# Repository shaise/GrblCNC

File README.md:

# GrblCNC
A C# Clone to LinuxCNC that works with GRBL CNC driver  
#### This project is done in parallel with a compatible Grbl driver firmware
* [Click here for project page](https://github.com/shaise/grblHAL_CNC3040)
```diff
- This is a work in progress, only basic stuff are operational  
```
## Software
### Screen preview 

## Hardware
* [Click here for firmware project page](https://github.com/shaise/grblHAL_CNC3040)
* [Click here for project progress](PROGRESS.md)
* [Click here for list of added capabilities](EXTENTIONS.md)
### GRBL for Chinese CNC3040-like machines. WIP. 
### Based on STM32F103C8T6 "Bluepill" boards with customized grblHAL firmware 
#### Project goals: 
* Develop simple open hardware plug to replace the vanishing parallel port
    - Support configurable pin assignments
    - Support extra controls not available on CNC3040 such as mist, flood, spindle RPM reader
* Add support for more axis. (at least add A axis)
* Support other features that LinuxCNC have

## Development Environment
|                      |                          |
|----------------------|--------------------------|
| **IDE**              | STM32CubeIDE v1.2.0      |
| **Controller board** | STM32F103C8T6 (Bluepill) |

## Reference
- GRBL CNC controller ported to STM32 controller (and others)
```https://github.com/terjeio/grblHAL```
- GRBL CNC controller
```https://github.com/gnea/grbl```

## Pin Diagram

## GRBL dongle for CNC3040 concept art:

### Back side

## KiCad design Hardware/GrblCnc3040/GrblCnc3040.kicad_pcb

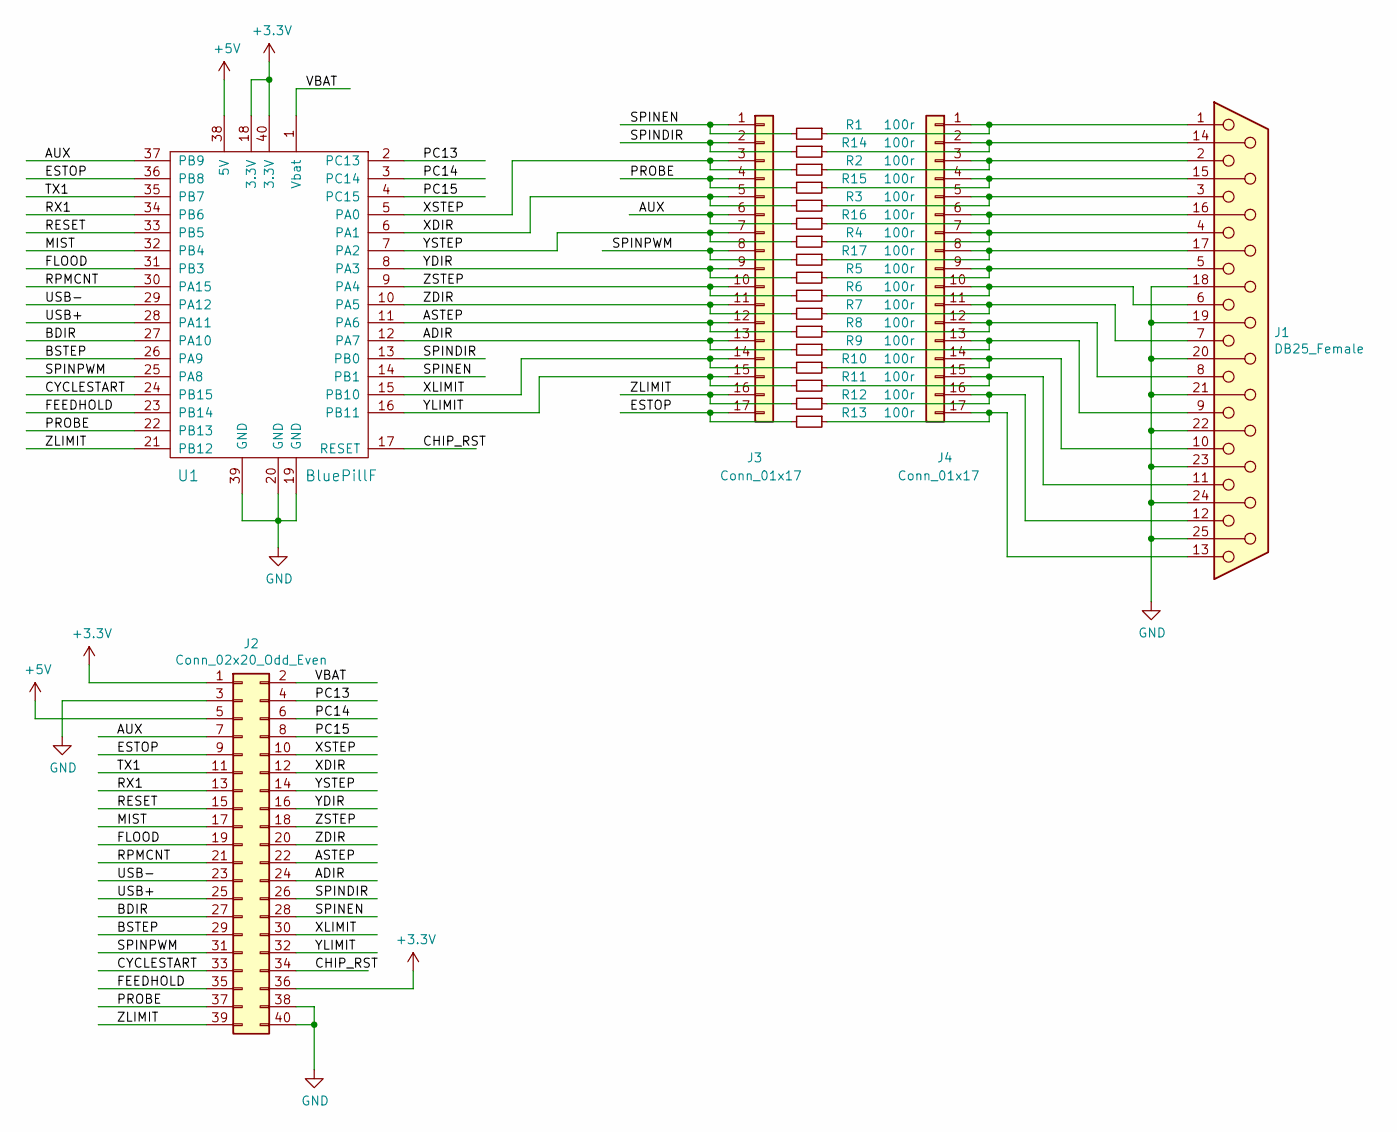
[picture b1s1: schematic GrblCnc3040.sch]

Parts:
J1: DB25_Female; DSUB-25_Female_Horizontal_P2.77x2.84mm_EdgePinOffset4.94mm_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
J2: Conn_02x20_Odd_Even; PinSocket_2x20_P2.54mm_Vertical
J3, J4: Conn_01x17; PinHeader_1x17_P2.54mm_Vertical
R1, R2, R3, R4, R5, R6, R7, R8, R9, R10, R11, R12, R13, R14, R15, R16, R17: 100r; R_0603_1608Metric
U1: BluePillF; BluePill_STM32F103C

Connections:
+3V3: J2.1, J2.36, U1.18 (3.3V), U1.40 (3.3V)
+5V: J2.5, U1.38 (5V)
/ADIR: J2.24, J3.13, R9.2, U1.12 (PA7)
/ASTEP: J2.22, J3.12, R8.2, U1.11 (PA6)
/AUX: J2.7, J3.6, R16.2, U1.37 (PB9)
/BDIR: J2.27, U1.27 (PA10)
/BSTEP: J2.29, U1.26 (PA9)
/CHIP_RST: J2.34, U1.17 (RESET)
/CYCLESTART: J2.33, U1.24 (PB15)
/ESTOP: J2.9, J3.17, R13.2, U1.36 (PB8)
/FEEDHOLD: J2.35, U1.23 (PB14)
/FLOOD: J2.19, U1.31 (PB3)
/MIST: J2.17, U1.32 (PB4)
/PC13: J2.4, U1.2 (PC13)
/PC14: J2.6, U1.3 (PC14)
/PC15: J2.8, U1.4 (PC15)
/PROBE: J2.37, J3.4, R15.2, U1.22 (PB13)
/RESET: J2.15, U1.33 (PB5)
/RPMCNT: J2.21, U1.30 (PA15)
/RX1: J2.13, U1.34 (PB6)
/SPINDIR: J2.26, J3.2, R14.2, U1.13 (PB0)
/SPINEN: J2.28, J3.1, R1.2, U1.14 (PB1)
/SPINPWM: J2.31, J3.8, R17.2, U1.25 (PA8)
/TX1: J2.11, U1.35 (PB7)
/USB+: J2.25, U1.28 (PA11)
/USB-: J2.23, U1.29 (PA12)
/VBAT: J2.2, U1.1 (Vbat)
/XDIR: J2.12, J3.5, R3.2, U1.6 (PA1)
/XLIMIT: J2.30, J3.14, R10.2, U1.15 (PB10)
/XSTEP: J2.10, J3.3, R2.2, U1.5 (PA0)
/YDIR: J2.16, J3.9, R5.2, U1.8 (PA3)
/YLIMIT: J2.32, J3.15, R11.2, U1.16 (PB11)
/YSTEP: J2.14, J3.7, R4.2, U1.7 (PA2)
/ZDIR: J2.20, J3.11, R7.2, U1.10 (PA5)
/ZLIMIT: J2.39, J3.16, R12.2, U1.21 (PB12)
/ZSTEP: J2.18, J3.10, R6.2, U1.9 (PA4)
GND: J1.18, J1.19, J1.20, J1.21, J1.22, J1.23, J1.24, J1.25, J2.3, J2.38, J2.40, U1.19 (GND), U1.20 (GND), U1.39 (GND)
unnamed: J1.1, J4.1, R1.1
unnamed: J1.2, J4.3, R2.1
unnamed: J1.3, J4.5, R3.1
unnamed: J1.4, J4.7, R4.1
unnamed: J1.5, J4.9, R5.1
unnamed: J1.6, J4.10, R6.1
unnamed: J1.7, J4.11, R7.1
unnamed: J1.8, J4.12, R8.1
unnamed: J1.9, J4.13, R9.1
unnamed: J1.10, J4.14, R10.1
unnamed: J1.11, J4.15, R11.1
unnamed: J1.12, J4.16, R12.1
unnamed: J1.13, J4.17, R13.1
unnamed: J1.14, J4.2, R14.1
unnamed: J1.15, J4.4, R15.1
unnamed: J1.16, J4.6, R16.1
unnamed: J1.17, J4.8, R17.1

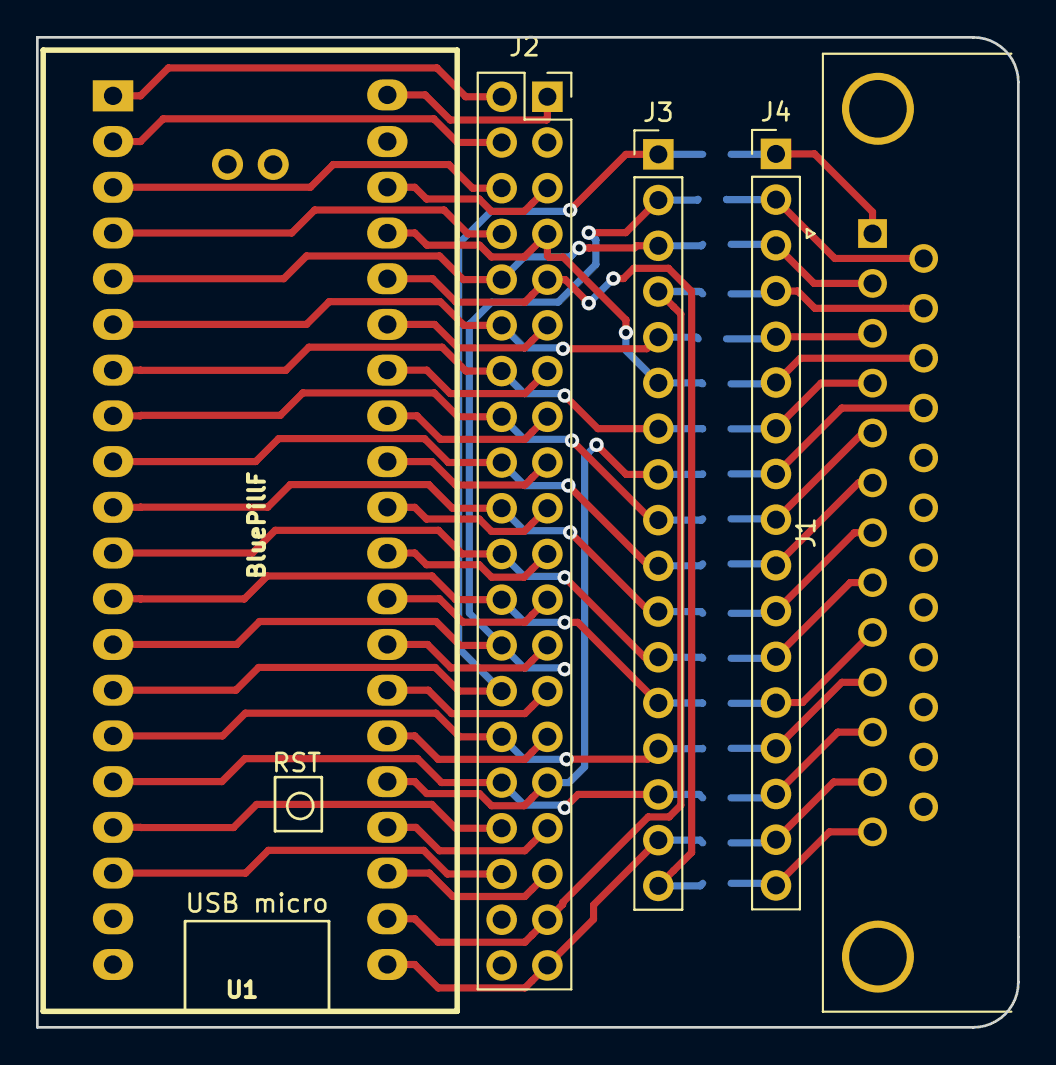
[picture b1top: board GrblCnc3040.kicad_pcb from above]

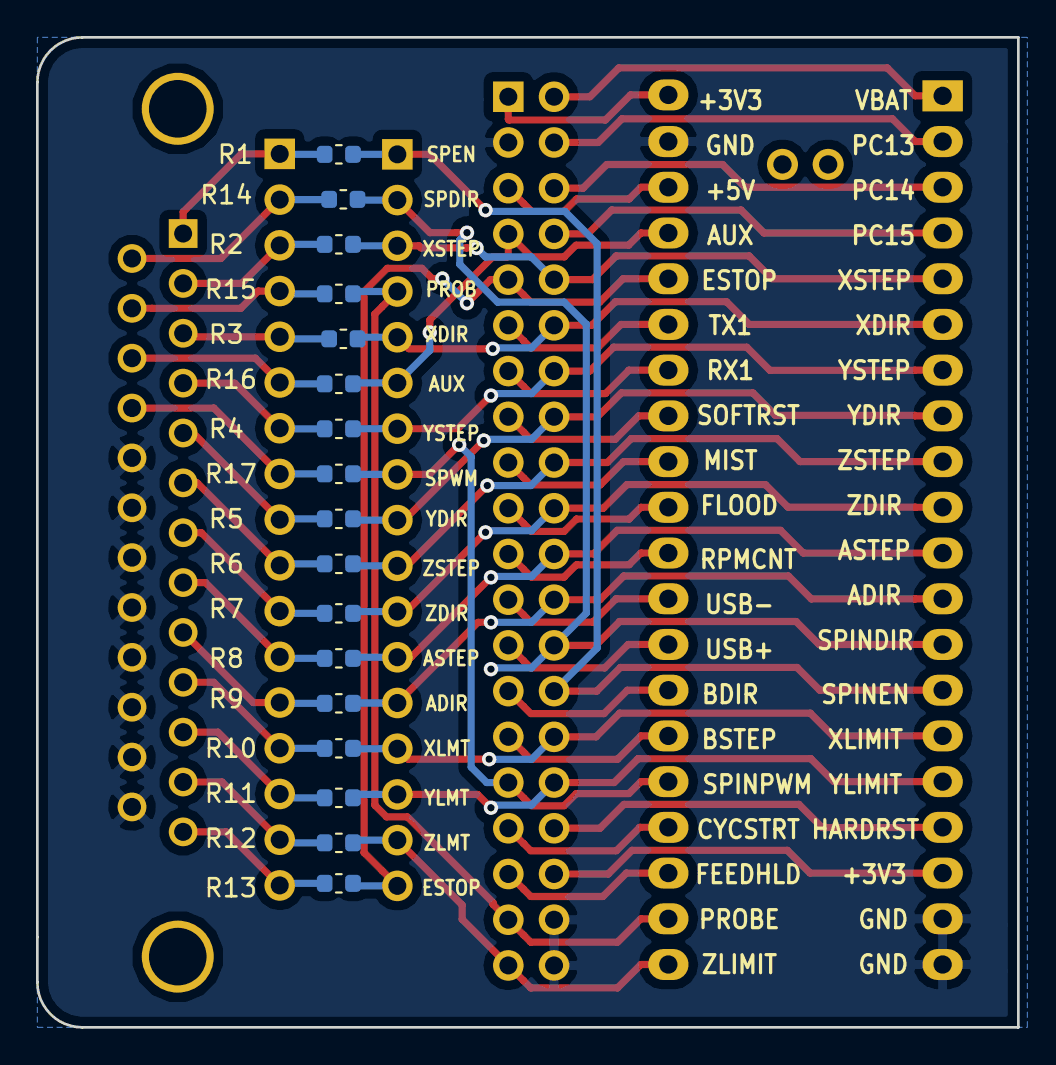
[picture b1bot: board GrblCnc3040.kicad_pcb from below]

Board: 2 copper layers, 54.5 x 55.0 mm, 22 parts (17 on the bottom side), 54 nets.

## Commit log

2020-03-20 add image
2020-03-20 project placeholder
2020-03-27 Add basic doc files
2020-03-27 Add Hardware files
2020-03-27 Add software files
2020-03-27 Implement most of toolbar buttons
2020-03-28 update progress
2020-03-29 Add dimention lines to gcode 3d viewer
2020-03-30 fix camera motion
2020-03-30 Use "." decimal notation for all grble float transactions. Issue #1 Change Glutils to Utils for scope simplification
2020-03-30 Make all display use '.' decimal notation as well. Issue #1
2020-03-30 Add todo list
2020-03-30 Add Feed/RPM status view. fix duplication of dimensions when loading new gcode.
2020-03-30 Initial support of g54-59 offsets
2020-03-30 remove VS suo file
2020-03-31 Some changes to the manual control
2020-04-02 display of gcode parser state
2020-04-02 add missing files
2020-04-02 add WCO overlay on 3d window
2020-04-03 Support coordinate touch-off
2020-04-05 support probing
2020-04-06 support display of errors similar to LinuxCNC
2020-04-06 support spindle operation
2020-04-07 Begin implementation of a user friendly GRBL configurator
2020-04-07 change horizontal tab ui slightly
2020-04-09 Continue parameter editor
2020-04-09 highlight changes ob edit parameters
2020-04-10 Complete Detailed UI for configuring Grbl driver
2020-04-11 disable program button when there are no changes
2020-04-11 fix crash when there are empty lines in gcode. Issue #2.
2020-04-11 add timeout to serial port writings. Prevent hangs when auto probing ports, Issue #3.
2020-04-11 Display current grbl motion mode. Fix stop gcode behaviour.
2020-04-12 start tool table implementation
2020-04-12 remove renamed files
2020-04-12 continue tool table
2020-04-13 Design (not functional yet) Tool table editor
2020-04-14 continue tool table gui
2020-04-16 Add manual tool changing popup
2020-04-18 Tool changing implemented
2020-04-20 complete support for tool touch off and probing
2020-04-23 cleanup many small bugs. Project is ready for initial release
2020-04-24 Adapt to newest grblHAL firmware
2020-05-01 remove grbl conf tab
2020-05-03 finalize homing system. check and fix other small issues
2020-05-03 Add about dialog
2020-05-04 final preperation for release V0.01
2020-05-04 update readmes
2020-05-04 remove unneeded files
2020-05-04 remove bmpfont debug saving
2020-06-07 fix typo
2022-10-07 small fixes. support lower number of axis
2023-08-28 adapt to general grblHal devices add support for communication devices other then serial
2023-11-23 add network support
2023-12-31 support empty string settings
2024-01-01 add goto form
2024-01-04 add goto functionality
2024-01-07 fix some compatibility issues
2024-01-10 fix a,b axis goto limits
2024-01-11 move net probing to a separate thread
2024-01-14 add feed override
2024-01-16 add speed ovverides and fix some thread locks.
2024-01-21 remember last value per axis on probe forms
2024-02-24 add 'invert pwm' bit
2024-02-25 improve probing system
2024-02-26 probe hole wip
2024-02-26 complete center hole probe
2024-03-06 use built in grblhal parameter description
2024-04-16 Support gcode macros
2025-02-23 fix end of gcode not resetting. add function keys
2025-07-10 small shader fix
2025-07-12 handle exceptions on port detection. fix goto resolution.
2026-05-19 fix small arcs issue
